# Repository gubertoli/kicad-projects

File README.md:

# kicad-projects
Some KiCAD PCB Designs

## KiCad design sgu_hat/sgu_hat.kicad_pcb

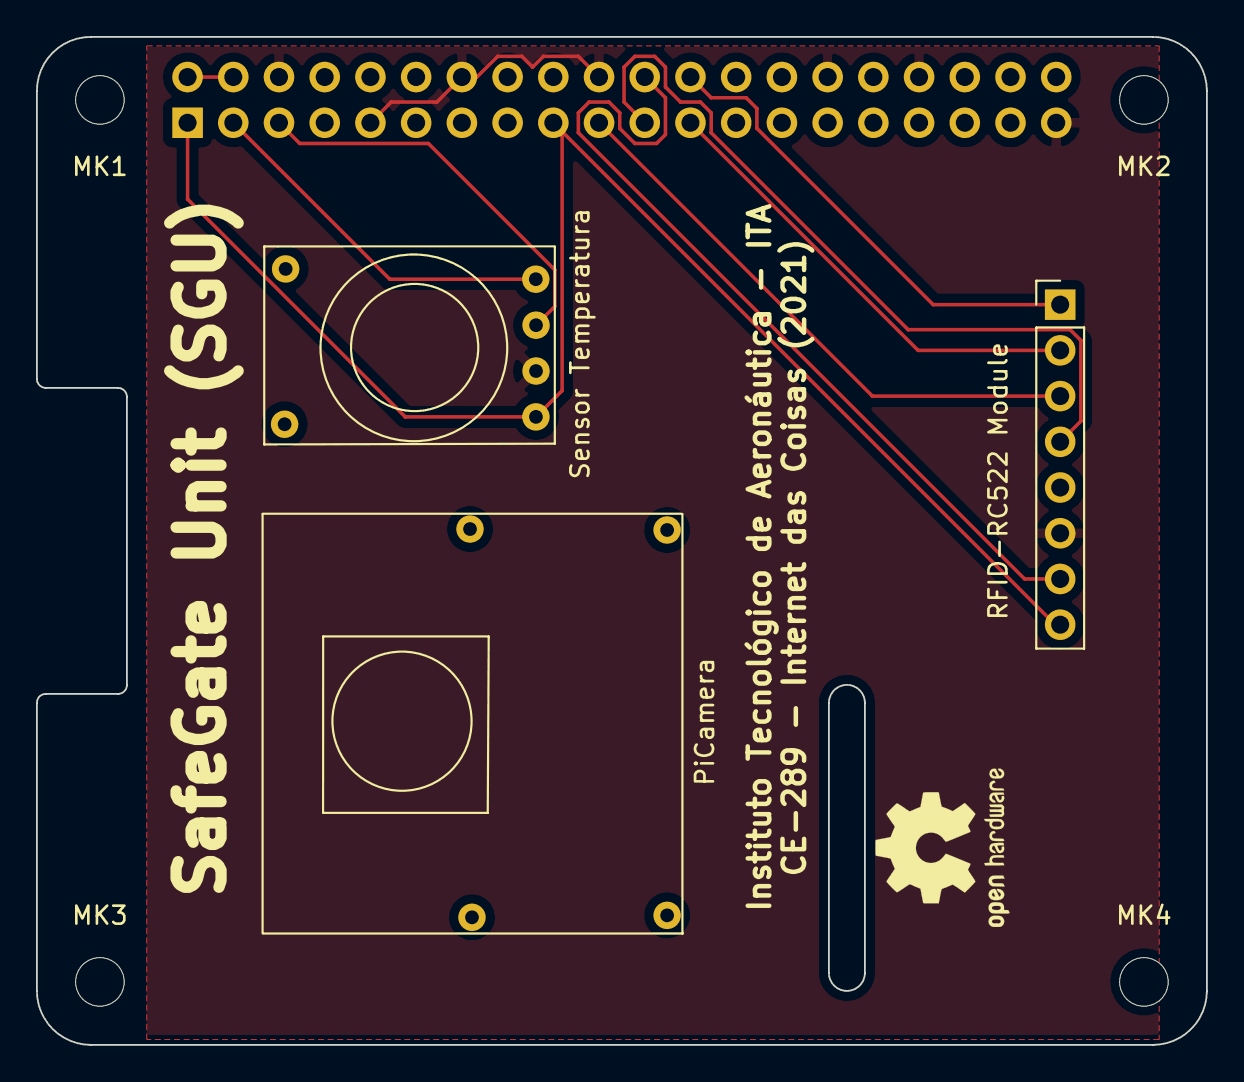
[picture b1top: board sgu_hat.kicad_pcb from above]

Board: 2 copper layers, 65.0 x 56.0 mm, 8 parts (1 on the bottom side), 10 nets.

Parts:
MK1, MK2, MK3, MK4: M2.5; MountingHole_2.7mm_M2.5
P1: Conn_02x20_Odd_Even; PinSocket_2x20_P2.54mm_Vertical
PiCamera: Camera_Lens; PiCamera
RFID-RC522 Module: RFID-RC522-MODULE; PinHeader_1x08_P2.54mm_Vertical
Sensor Temperatura: MLX90614ESF-AAA-000-TU; MLX90614_Shield

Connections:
+3V3: P1.1, P1.17, RFID-RC522 Module.8, Sensor Temperatura.VIN
+5V: P1.2, P1.4
/GPIO2(SDA1): P1.3, Sensor Temperatura.1
/GPIO3(SCL1): P1.5, Sensor Temperatura.SCL
/GPIO8(SPI0_CE_N): P1.24, RFID-RC522 Module.1
/GPIO9(SPI0_MISO): P1.21, RFID-RC522 Module.4
/GPIO10(SPI0_MOSI): P1.19, RFID-RC522 Module.3
/GPIO11(SPI0_SCK): P1.23, RFID-RC522 Module.2
/GPIO25(GEN6): P1.22, RFID-RC522 Module.7
GND: P1.6, P1.9, P1.14, P1.20, P1.25, P1.30, P1.34, P1.39, RFID-RC522 Module.6, Sensor Temperatura.GND

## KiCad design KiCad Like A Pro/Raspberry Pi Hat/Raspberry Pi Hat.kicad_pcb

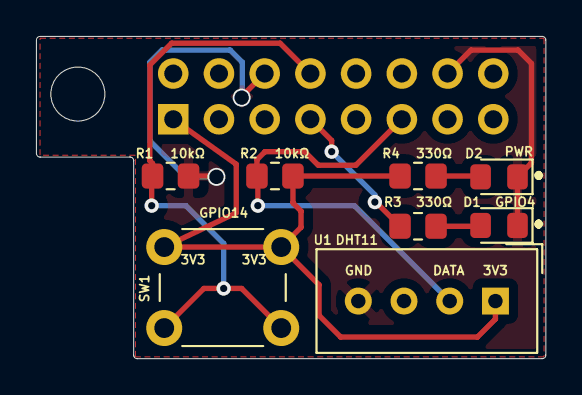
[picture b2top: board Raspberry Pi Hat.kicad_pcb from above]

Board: 2 copper layers, 28.3 x 17.9 mm, 9 parts (1 on the bottom side), 7 nets.

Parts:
D1: GPIO4; LED_0805_2012Metric_Pad1.15x1.40mm_HandSolder
D2: PWR; LED_0805_2012Metric_Pad1.15x1.40mm_HandSolder
J1: Raspberry_Pi_2_3; PinSocket_2x08_P2.54mm_Vertical
R1, R2: 10kΩ; R_0805_2012Metric_Pad1.20x1.40mm_HandSolder
R3, R4: 330Ω; R_0805_2012Metric_Pad1.20x1.40mm_HandSolder
SW1: GPIO14; SW_PUSH_6mm
U1: DHT11; Aosong_DHT11_5.5x12.0_P2.54mm

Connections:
/3V3: J1.1, R2.2, R4.1, SW1.1, U1.1
/BUTTON: J1.8, R1.1, SW1.2
/DHT: J1.11, R2.1, U1.2
GND: D1.1, D2.1, J1.6, J1.9, J1.14, R1.2, U1.4
unnamed: D1.2, R3.2
unnamed: D2.2, R4.2
unnamed: J1.7, R3.1

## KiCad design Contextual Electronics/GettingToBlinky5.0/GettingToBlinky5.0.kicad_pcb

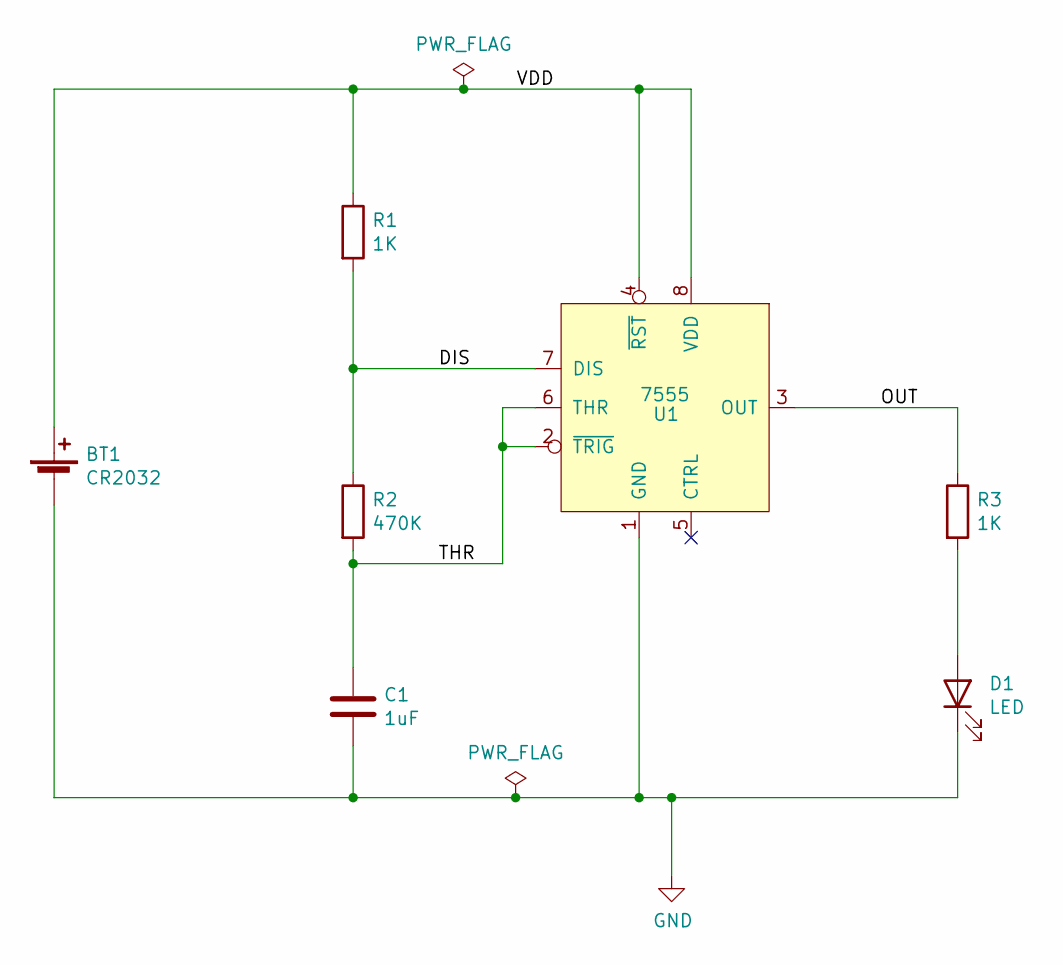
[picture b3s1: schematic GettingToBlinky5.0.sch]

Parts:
BT1: CR2032; S8211-46R
C1: 1uF; C_0805_2012Metric_Pad1.18x1.45mm_HandSolder
D1: LED; LED_0805_2012Metric_Pad1.15x1.40mm_HandSolder
R1, R3: 1K; R_0805_2012Metric_Pad1.20x1.40mm_HandSolder
R2: 470K; R_0805_2012Metric_Pad1.20x1.40mm_HandSolder
U1: 7555; SOIC-8_3.9x4.9mm_P1.27mm

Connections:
/DIS: R1.2, R2.1, U1.7 (DIS)
/OUT: R3.1, U1.3 (OUT)
/THR: C1.1, R2.2, U1.2 (~TRIG), U1.6 (THR)
/VDD: BT1.1 (+), R1.1, U1.4 (~RST), U1.8 (VDD)
GND: BT1.2 (-), C1.2, D1.1 (K), U1.1 (GND)
unnamed: D1.2 (A), R3.2

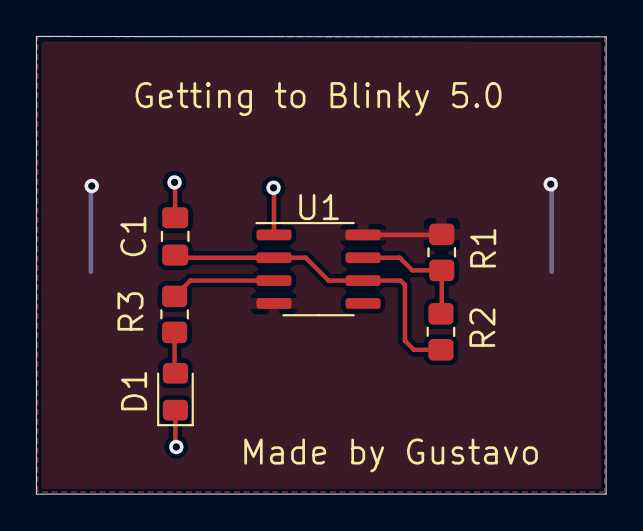
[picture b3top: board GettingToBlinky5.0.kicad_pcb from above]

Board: 2 copper layers, 31.6 x 25.4 mm, 7 parts (1 on the bottom side), 6 nets.

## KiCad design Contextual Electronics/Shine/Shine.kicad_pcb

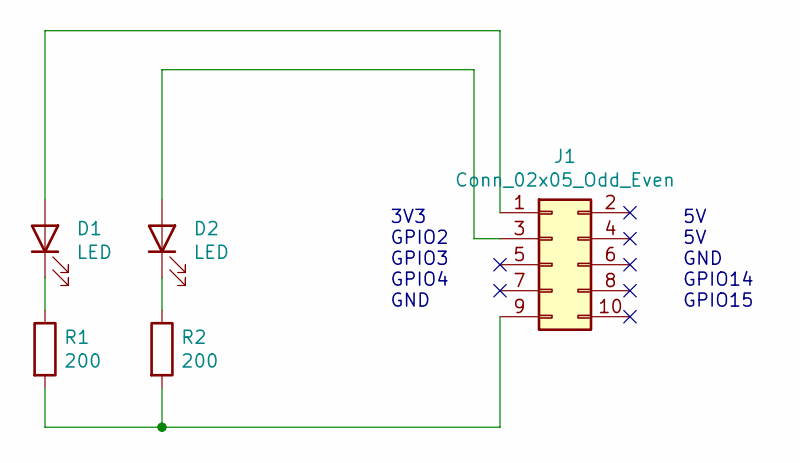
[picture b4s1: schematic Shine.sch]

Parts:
D1, D2: LED; LED_1206_3216Metric_Pad1.42x1.75mm_HandSolder
J1: Conn_02x05_Odd_Even; PinHeader_2x05_P2.54mm_Vertical
R1, R2: 200; R_1206_3216Metric_Pad1.30x1.75mm_HandSolder

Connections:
unnamed: D1.1 (K), R1.1
unnamed: D1.2 (A), J1.1
unnamed: D2.1 (K), R2.1
unnamed: D2.2 (A), J1.3
unnamed: J1.9, R1.2, R2.2

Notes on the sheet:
3V3 GPIO2 GPIO3 GPIO4 GND
5V 5V GND GPIO14 GPIO15

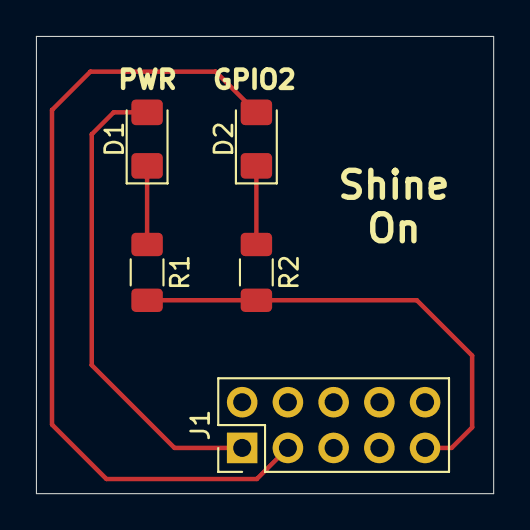
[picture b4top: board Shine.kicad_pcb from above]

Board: 2 copper layers, 25.4 x 25.4 mm, 5 parts (0 on the bottom side), 5 nets.

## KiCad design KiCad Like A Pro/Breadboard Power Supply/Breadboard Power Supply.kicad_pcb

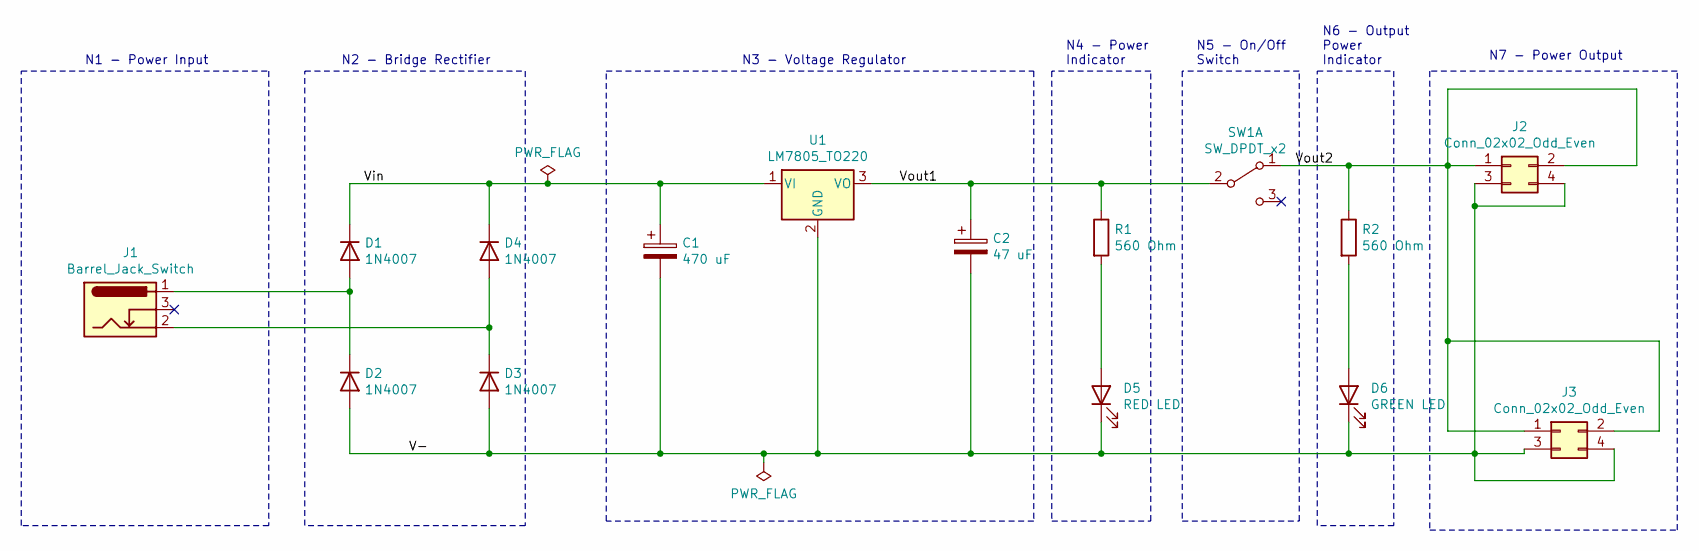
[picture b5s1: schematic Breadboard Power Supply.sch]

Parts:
C1: 470 uF; CP_Radial_D10.0mm_P5.00mm
C2: 47 uF; CP_Radial_D6.3mm_P2.50mm
D1, D2, D3, D4: 1N4007; D_DO-41_SOD81_P10.16mm_Horizontal
D5: RED LED; LED_D5.0mm
D6: GREEN LED; LED_D5.0mm
J1: Barrel_Jack_Switch; BarrelJack_CUI_PJ-102AH_Horizontal
J2, J3: Conn_02x02_Odd_Even; PinHeader_2x02_P2.54mm_Vertical
R1, R2: 560 Ohm; R_Axial_DIN0207_L6.3mm_D2.5mm_P7.62mm_Horizontal
SW1: SW_DPDT_x2; Switch_Slide_11.6x4mm_EG1218
U1: LM7805_TO220; TO-220-3_Vertical

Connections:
/V-: C1.2, C2.2, D2.2 (A), D3.2 (A), D5.1 (K), D6.1 (K), J2.3, J2.4, J3.3, J3.4, U1.2 (GND)
/Vin: C1.1, D1.1 (K), D4.1 (K), U1.1 (VI)
/Vout1: C2.1, R1.1, SW1.2 (B), U1.3 (VO)
/Vout2: J2.1, J2.2, J3.1, J3.2, R2.1, SW1.1 (A)
unnamed: D1.2 (A), D2.1 (K), J1.1
unnamed: D3.1 (K), D4.2 (A), J1.2
unnamed: D5.2 (A), R1.2
unnamed: D6.2 (A), R2.2

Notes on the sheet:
N1 - Power Input
N2 - Bridge Rectifier
N3 - Voltage Regulator
N4 - Power Indicator
N5 - On/Off Switch
N6 - Output Power Indicator
N7 - Power Output

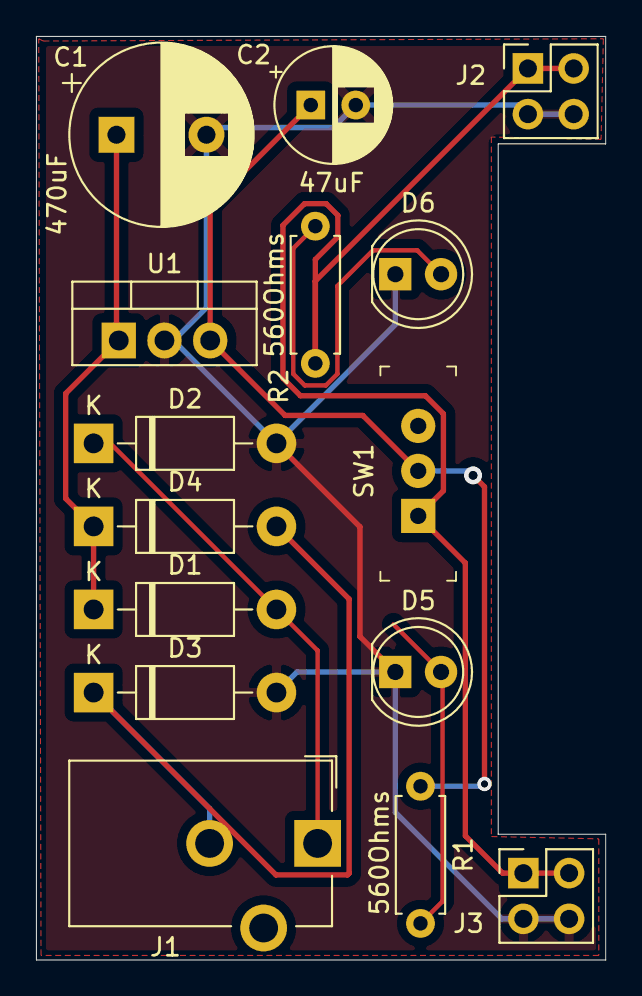
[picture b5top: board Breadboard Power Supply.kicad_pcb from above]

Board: 2 copper layers, 31.6 x 51.3 mm, 15 parts (0 on the bottom side), 8 nets.

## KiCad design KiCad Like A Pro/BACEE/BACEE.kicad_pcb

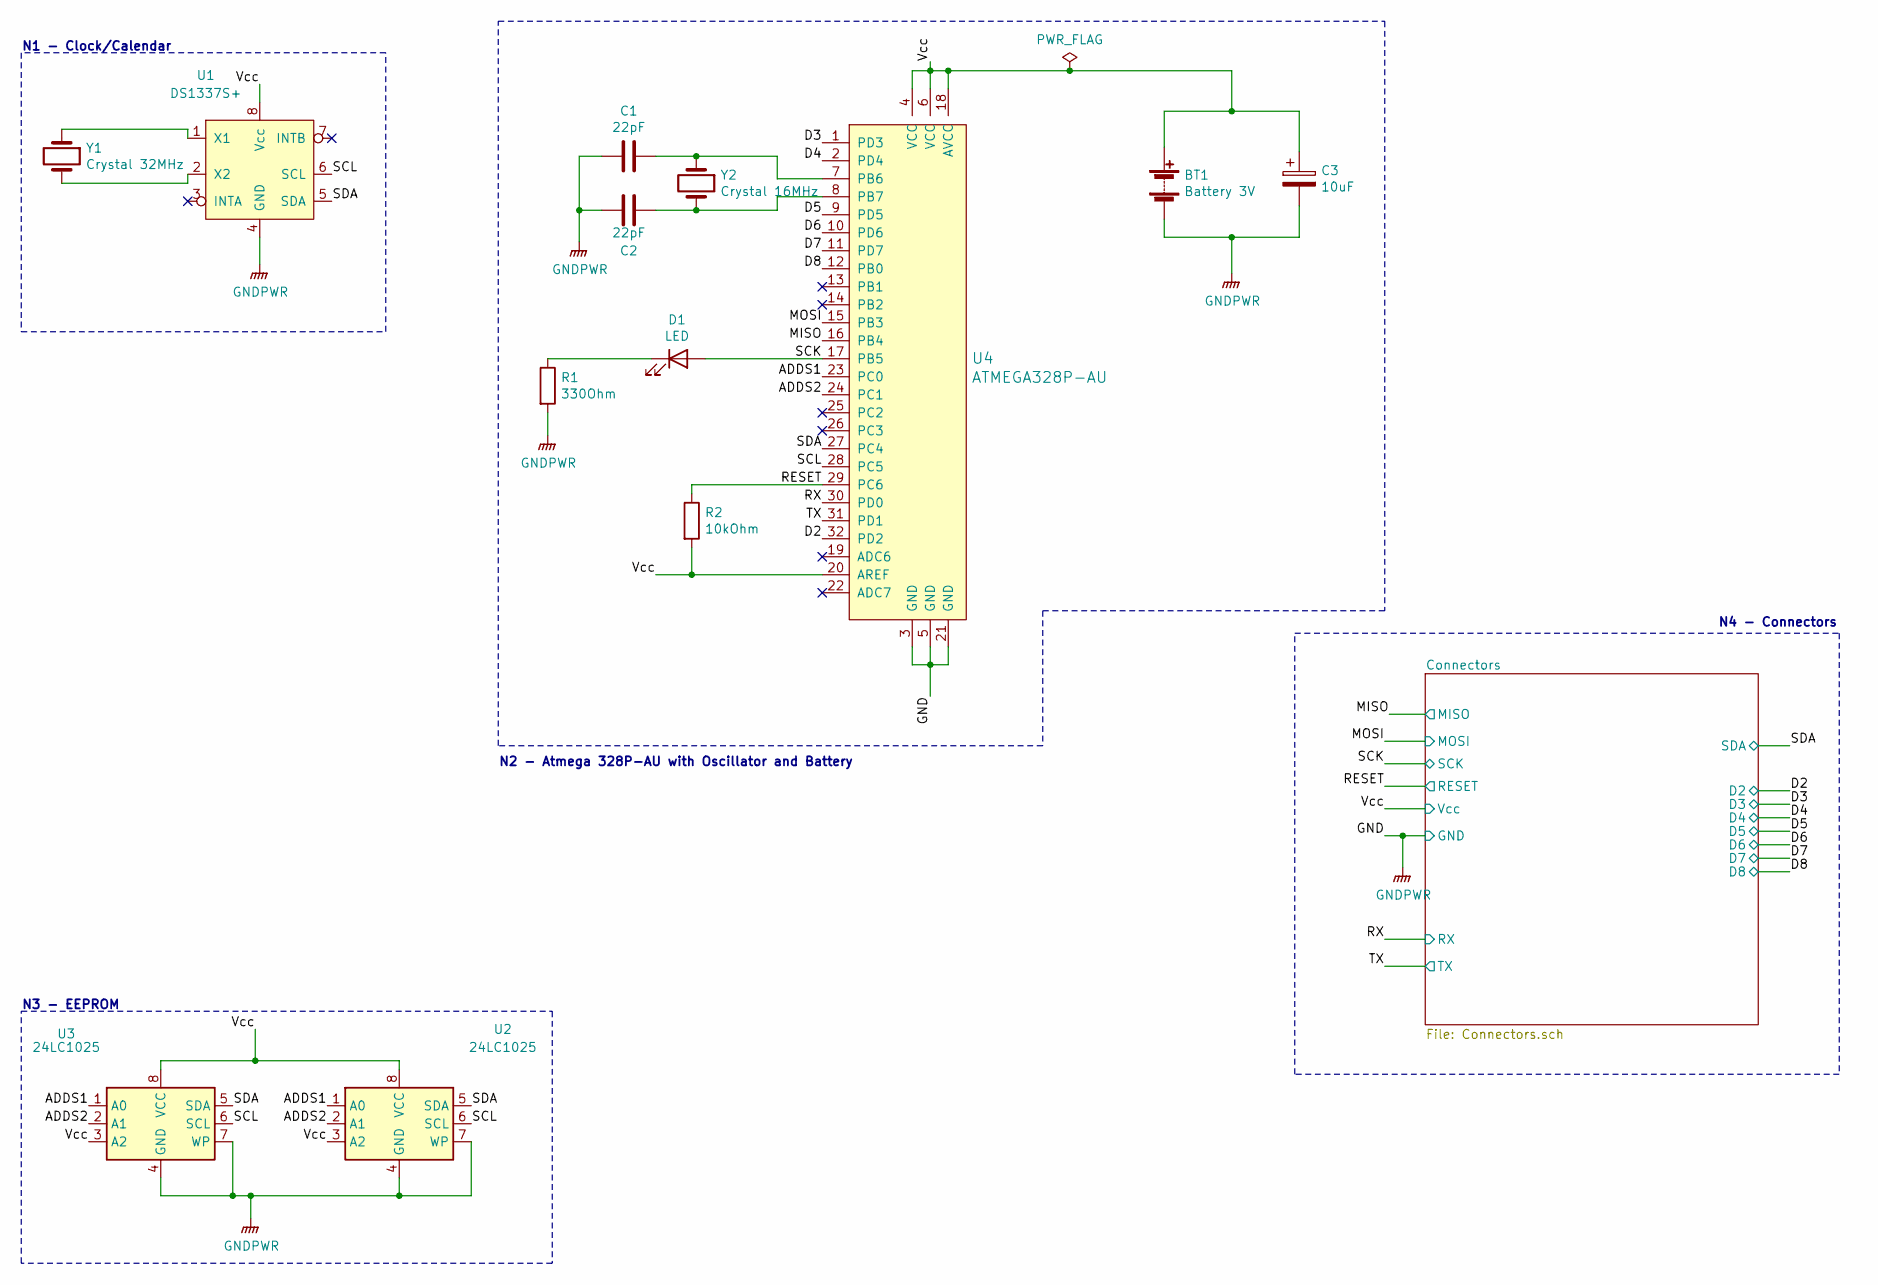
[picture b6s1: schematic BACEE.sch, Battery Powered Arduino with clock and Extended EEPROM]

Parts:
BT1: Battery 3V; PinHeader_1x02_P2.54mm_Vertical
C1, C2: 22pF; C_0805_2012Metric_Pad1.18x1.45mm_HandSolder
C3: 10uF; C_0805_2012Metric_Pad1.18x1.45mm_HandSolder
D1: LED; LED_0805_2012Metric_Pad1.15x1.40mm_HandSolder
R1: 330Ohm; R_0805_2012Metric_Pad1.20x1.40mm_HandSolder
R2: 10kOhm; R_0805_2012Metric_Pad1.20x1.40mm_HandSolder
U1: DS1337S+; SO-8_5.3x6.2mm_P1.27mm
U2, U3: 24LC1025; SOIJ-8_5.3x5.3mm_P1.27mm
U4: ATMEGA328P-AU; TQFP-32_7x7mm; MPN ATMEGA328P-AU; Digi-Key_PN ATMEGA328P-AU-ND
Y1: Crystal 32MHz; Crystal_SMD_MicroCrystal_CC7V-T1A-2Pin_3.2x1.5mm_HandSolder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
Y2: Crystal 16MHz; Crystal_SMD_5032-2Pin_5.0x3.2mm_HandSoldering

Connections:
/ADDS1: U2.1 (A0), U3.1 (A0), U4.23 (PC0)
/ADDS2: U2.2 (A1), U3.2 (A1), U4.24 (PC1)
/D2: U4.32 (PD2); also elsewhere on the board
/D3: U4.1 (PD3); also elsewhere on the board
/D4: U4.2 (PD4); also elsewhere on the board
/D5: U4.9 (PD5); also elsewhere on the board
/D6: U4.10 (PD6); also elsewhere on the board
/D7: U4.11 (PD7); also elsewhere on the board
/D8: U4.12 (PB0); also elsewhere on the board
/MISO: U4.16 (PB4); also elsewhere on the board
/MOSI: U4.15 (PB3); also elsewhere on the board
/RESET: R2.1, U4.29 (PC6); also elsewhere on the board
/RX: U4.30 (PD0); also elsewhere on the board
/SCK: D1.2 (A), U4.17 (PB5); also elsewhere on the board
/SCL: U1.6 (SCL), U2.6 (SCL), U3.6 (SCL), U4.28 (PC5)
/SDA: U1.5 (SDA), U2.5 (SDA), U3.5 (SDA), U4.27 (PC4); also elsewhere on the board
/TX: U4.31 (PD1); also elsewhere on the board
/Vcc: BT1.1 (+), C3.1, R2.2, U1.8 (Vcc), U2.3 (A2), U2.8 (VCC), U3.3 (A2), U3.8 (VCC), U4.4 (VCC), U4.6 (VCC), U4.18 (AVCC), U4.20 (AREF); also elsewhere on the board
GNDPWR: BT1.2 (-), C1.2, C2.1, C3.2, R1.2, U1.4 (GND), U2.4 (GND), U2.7 (WP), U3.4 (GND), U3.7 (WP), U4.3 (GND), U4.5 (GND), U4.21 (GND); also elsewhere on the board
unnamed: C1.1, U4.7 (PB6), Y2.1
unnamed: C2.2, U4.8 (PB7), Y2.2
unnamed: D1.1 (K), R1.1
unnamed: U1.1 (X1), Y1.1
unnamed: U1.2 (X2), Y1.2

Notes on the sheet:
N1 - Clock/Calendar
N3 - EEPROM
N2 - Atmega 328P-AU with Oscillator and Battery
N4 - Connectors

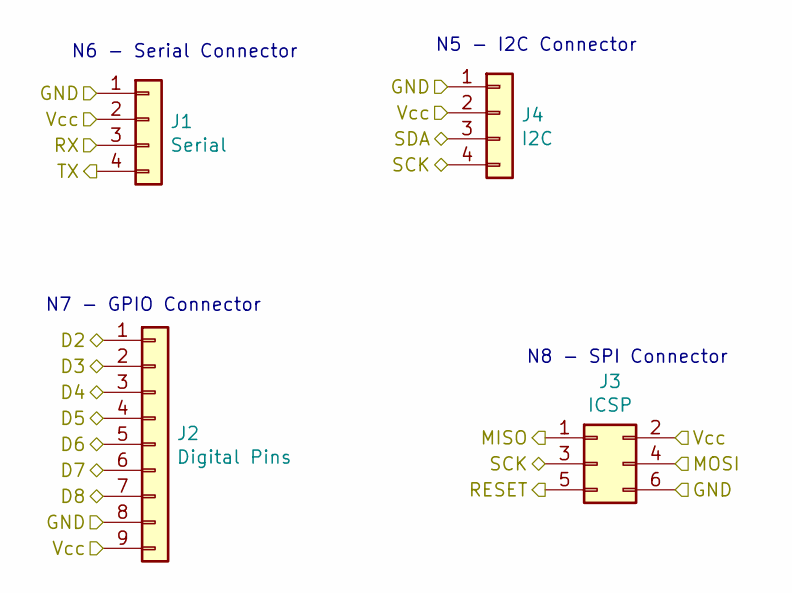
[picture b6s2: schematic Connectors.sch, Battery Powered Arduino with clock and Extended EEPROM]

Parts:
J1: Serial; PinSocket_1x04_P2.54mm_Vertical
J2: Digital Pins; PinSocket_1x09_P2.54mm_Vertical
J3: ICSP; PinSocket_2x03_P2.54mm_Vertical
J4: I2C; PinSocket_1x04_P2.54mm_Vertical

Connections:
/D2: J2.1; also elsewhere on the board
/D3: J2.2; also elsewhere on the board
/D4: J2.3; also elsewhere on the board
/D5: J2.4; also elsewhere on the board
/D6: J2.5; also elsewhere on the board
/D7: J2.6; also elsewhere on the board
/D8: J2.7; also elsewhere on the board
/MISO: J3.1; also elsewhere on the board
/MOSI: J3.4; also elsewhere on the board
/RESET: J3.5; also elsewhere on the board
/RX: J1.3; also elsewhere on the board
/SCK: J3.3, J4.4; also elsewhere on the board
/SDA: J4.3; also elsewhere on the board
/TX: J1.4; also elsewhere on the board
/Vcc: J1.2, J2.9, J3.2, J4.2; also elsewhere on the board
GNDPWR: J1.1, J2.8, J3.6, J4.1; also elsewhere on the board

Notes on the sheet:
N6 - Serial Connector
N5 - I2C Connector
N7 - GPIO Connector
N8 - SPI Connector

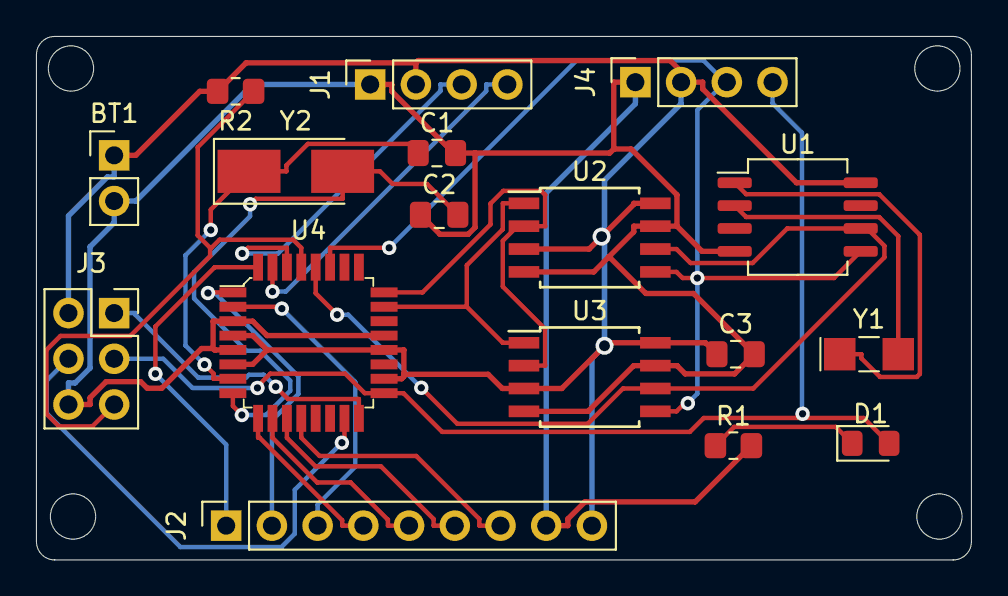
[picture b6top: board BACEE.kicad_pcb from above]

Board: 4 copper layers, 51.9 x 29.1 mm, 17 parts (0 on the bottom side), 24 nets.

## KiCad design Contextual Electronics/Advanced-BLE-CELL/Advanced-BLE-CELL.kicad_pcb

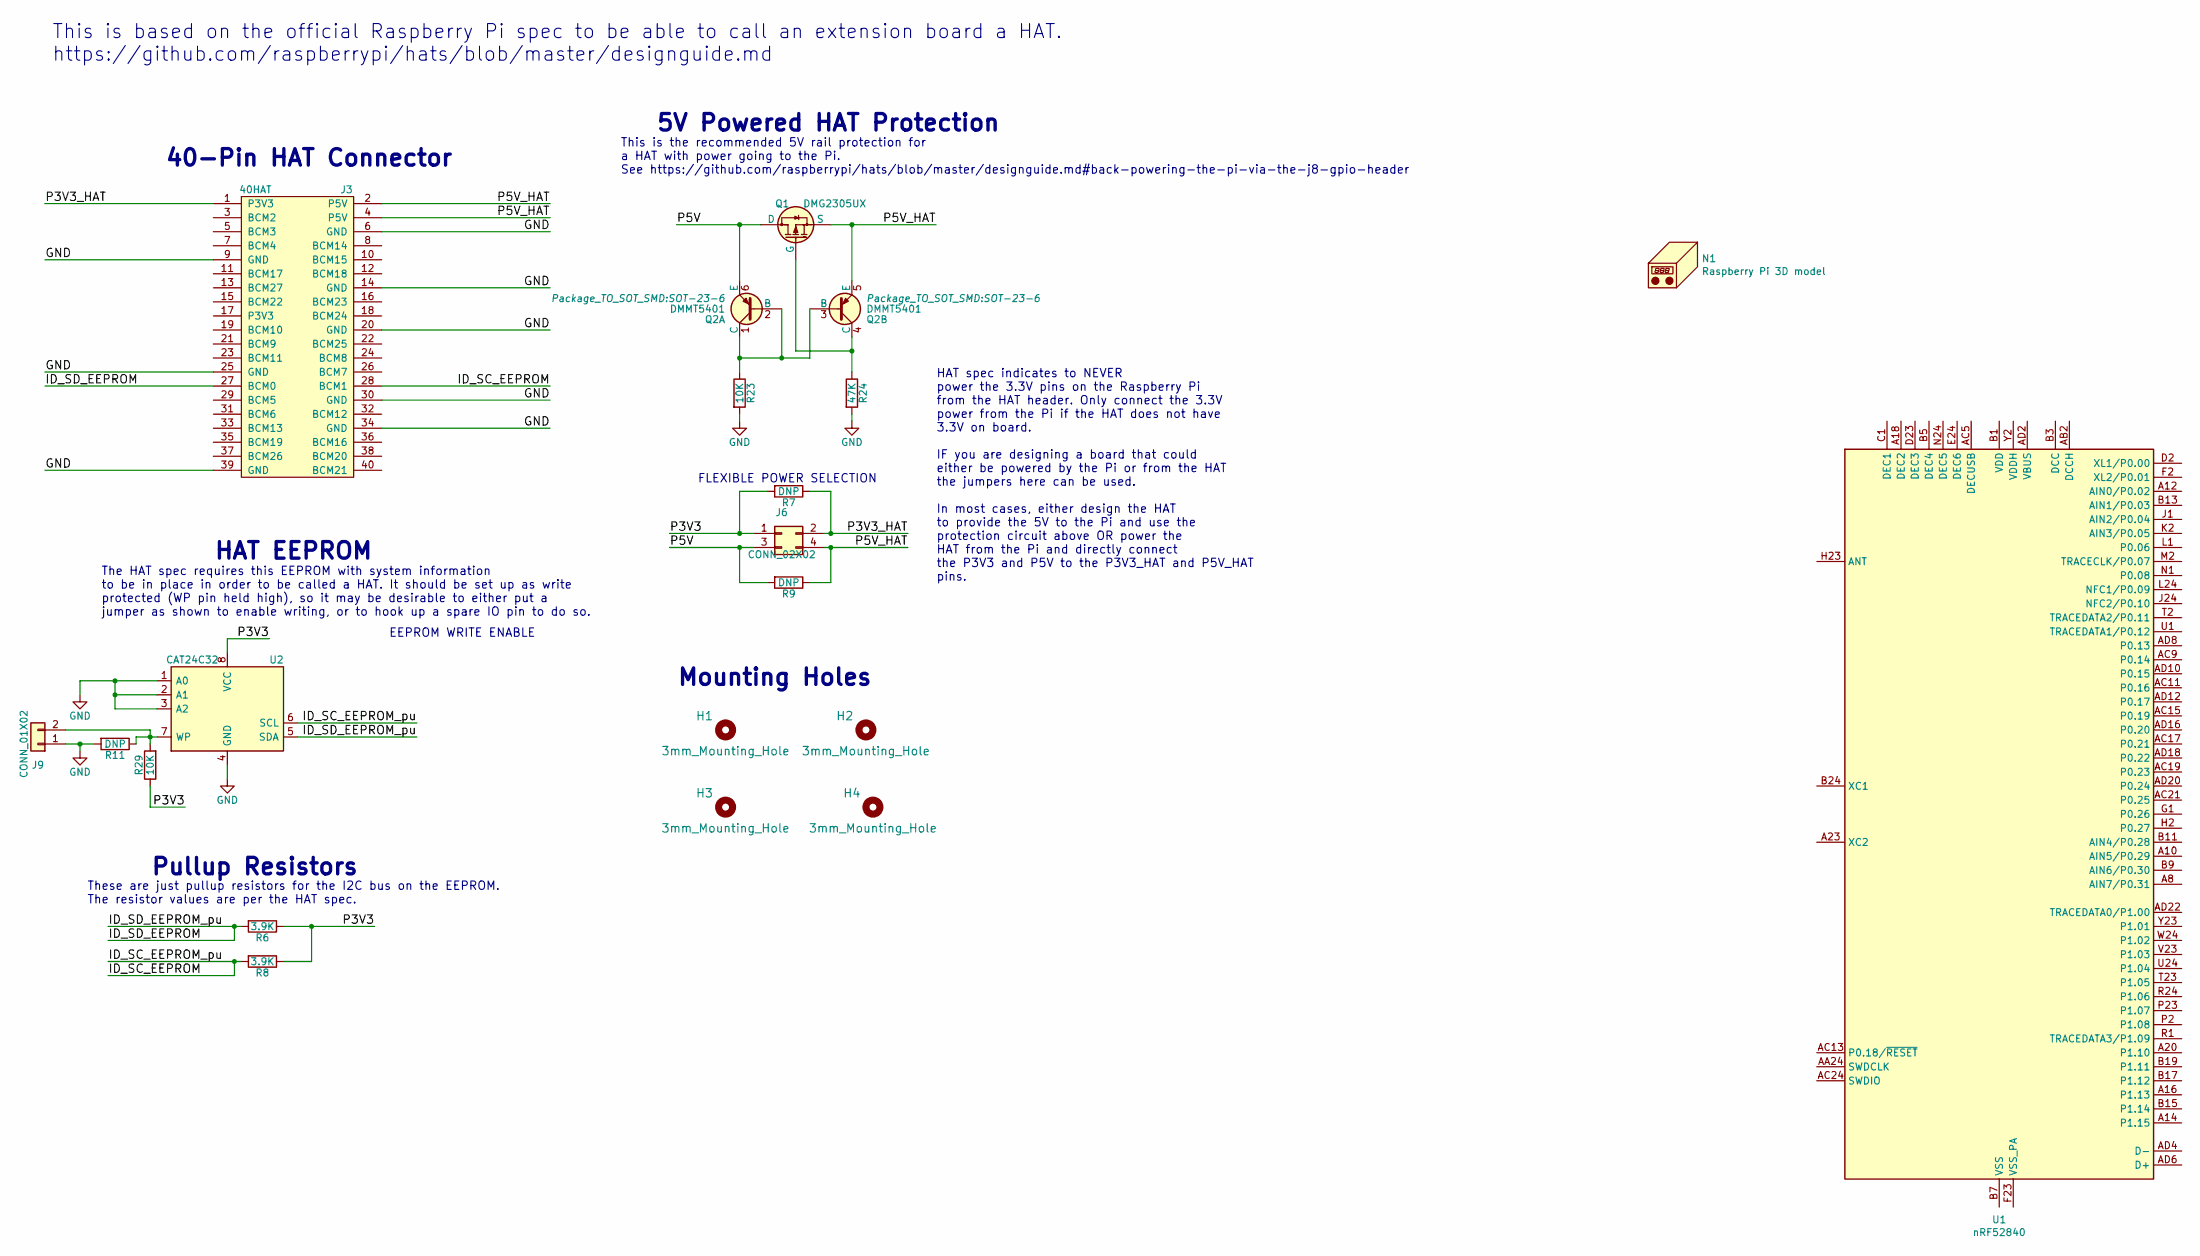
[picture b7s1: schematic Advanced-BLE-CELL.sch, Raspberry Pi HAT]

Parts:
H1, H2, H3, H4: 3mm_Mounting_Hole; NPTH_3mm_ID
J3: 40HAT; PinSocket_2x20_P2.54mm_Vertical
J6: CONN_02X02; PinHeader_2x02_P2.54mm_Vertical
J9: CONN_01X02; PinHeader_1x02_P2.54mm_Vertical
N1: Raspberry Pi 3D model
Q1: DMG2305UX; SOT-23
Q2: DMMT5401; SOT-23-6
R6, R8: 3.9K; R_0603_1608Metric_Pad0.84x1.00mm_HandSolder
R7, R9, R11: DNP; R_0603_1608Metric_Pad0.84x1.00mm_HandSolder
R23, R29: 10K; R_0603_1608Metric_Pad0.84x1.00mm_HandSolder
R24: 47K; R_0603_1608Metric_Pad0.84x1.00mm_HandSolder
U1: nRF52840; Nordic_AQFN-73-1EP_7x7mm_P0.5mm
U2: CAT24C32; SOIC-8_3.9x4.9mm_P1.27mm

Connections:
/ID_SC_EEPROM: J3.28 (BCM1), R8.2, U2.6 (SCL)
/ID_SD_EEPROM: J3.27 (BCM0), R6.2, U2.5 (SDA)
/P3V3: J6.1, R6.1, R7.2, R8.1, R29.1, U2.8 (VCC)
/P3V3_HAT: J3.1 (P3V3), J6.2, R7.1
/P5V: J6.3, Q1.3 (D), Q2.6 (E), R9.2
/P5V_HAT: J3.2 (P5V), J3.4 (P5V), J6.4, Q1.2 (S), Q2.5 (E), R9.1
GND: J3.6 (GND), J3.9 (GND), J3.14 (GND), J3.20 (GND), J3.25 (GND), J3.30 (GND), J3.34 (GND), J3.39 (GND), J9.1, R11.2, R23.2, R24.2, U2.1 (A0), U2.2 (A1), U2.3 (A2), U2.4 (GND)
unnamed: J9.2, R11.1, R29.2, U2.7 (WP)
unnamed: Q1.1 (G), Q2.4 (C), R24.1
unnamed: Q2.1 (C), Q2.2 (B), Q2.3 (B), R23.1
unnamed: U1.A22 (VDD), U1.AD14 (VDD), U1.AD23 (VDD), U1.B1 (VDD), U1.W1 (VDD)
unnamed: U1.B7 (VSS), U1.EP (VSS)

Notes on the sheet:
FLEXIBLE POWER SELECTION
5V Powered HAT Protection
This is the recommended 5V rail protection for a HAT with power going to the Pi. See https://github.com/raspberrypi/hats/blob/master/designguide.md#back-powering-the-pi-via-the-j8-gpio-header
EEPROM WRITE ENABLE
Pullup Resistors
HAT EEPROM
Mounting Holes
40-Pin HAT Connector
HAT spec indicates to NEVER power the 3.3V pins on the Raspberry Pi from the HAT header. Only connect the 3.3V power from the Pi if the HAT does not have 3.3V on board. IF you are designing a board that could either be powered by the Pi or from the HAT the jumpers here can be used. In most cases, e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
The HAT spec requires this EEPROM with system information to be in place in order to be called a HAT. It should be set up as write protected (WP pin held high), so it may be desirable to either put a jumper as shown to enable writing, or to hook up a spare IO pin to do so.
These are just pullup resistors for the I2C bus on the EEPROM. The resistor values are per the HAT spec.
This is based on the official Raspberry Pi spec to be able to call an extension board a HAT. https://github.com/raspberrypi/hats/blob/master/designguide.md

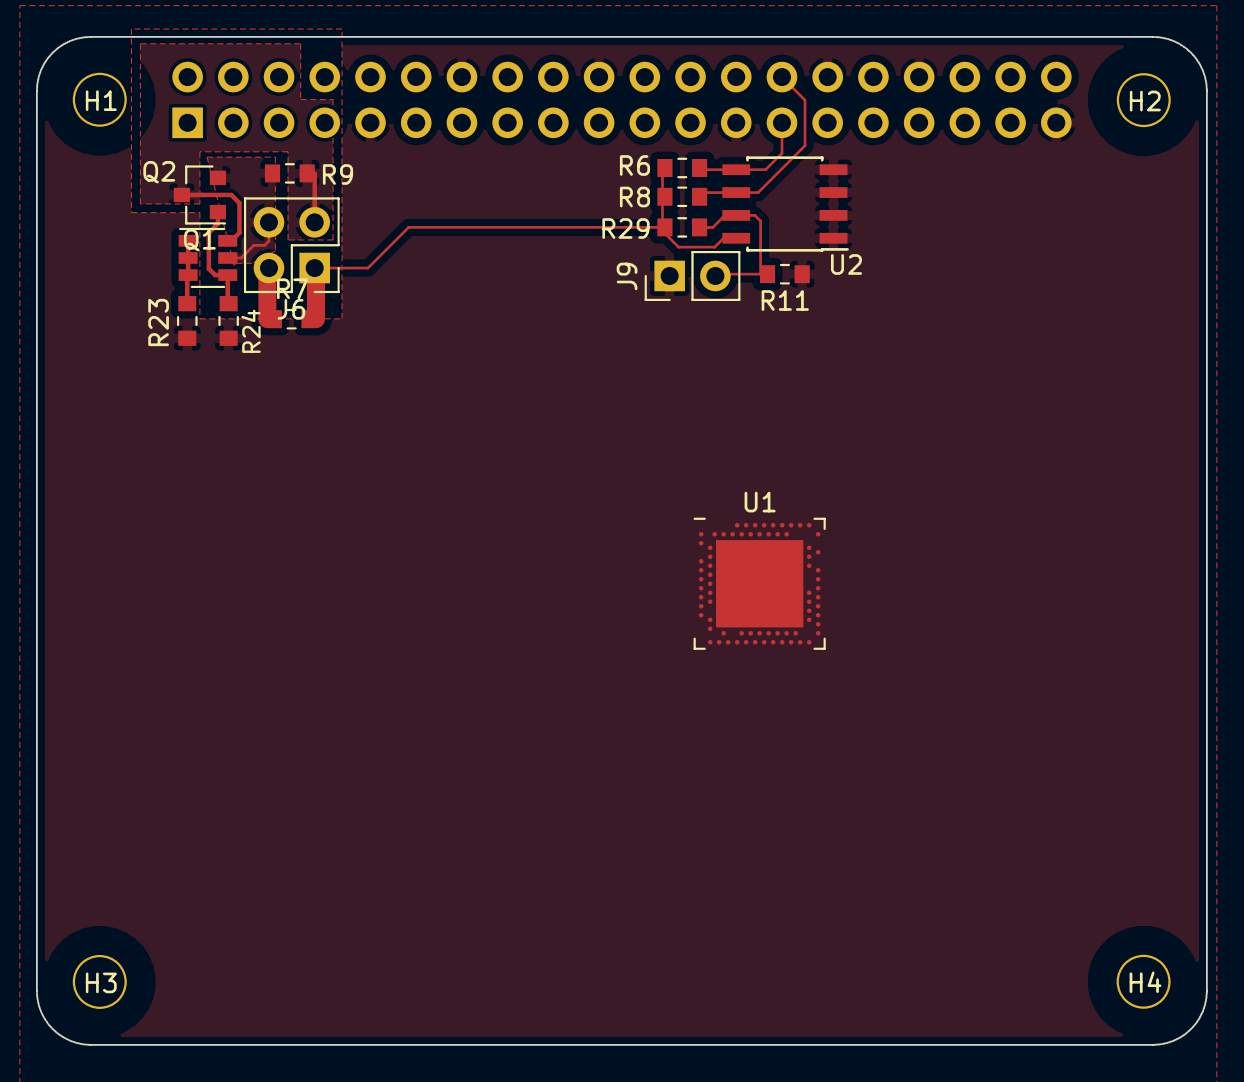
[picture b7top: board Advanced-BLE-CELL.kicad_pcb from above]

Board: 4 copper layers, 65.0 x 56.0 mm, 19 parts (1 on the bottom side), 12 nets.

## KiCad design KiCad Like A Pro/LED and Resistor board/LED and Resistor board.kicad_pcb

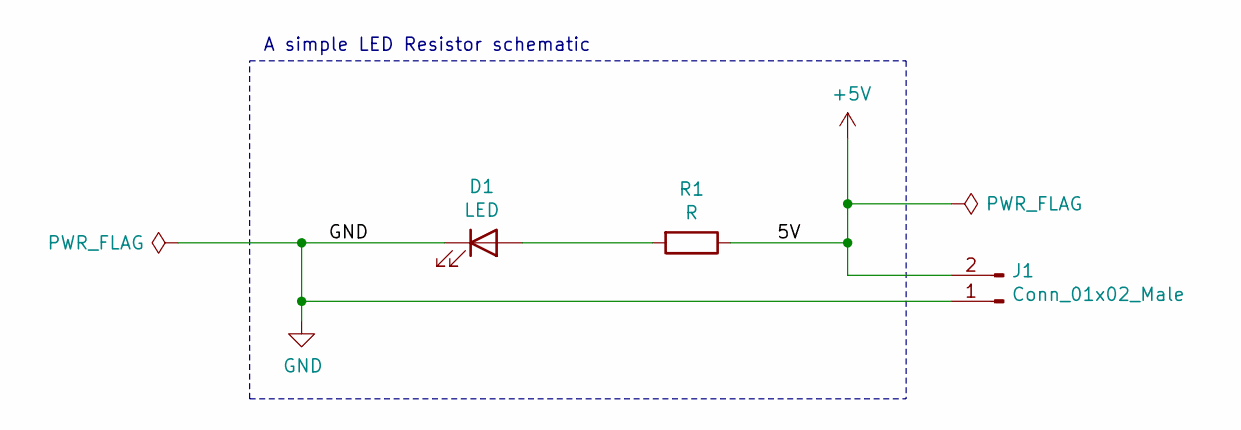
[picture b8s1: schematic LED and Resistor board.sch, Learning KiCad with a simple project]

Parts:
D1: LED; LED_D8.0mm
J1: Conn_01x02_Male; TerminalBlock_bornier-2_P5.08mm
R1: R; R_Axial_DIN0204_L3.6mm_D1.6mm_P5.08mm_Horizontal

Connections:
+5V: J1.2, R1.1
GND: D1.1 (K), J1.1
unnamed: D1.2 (A), R1.2

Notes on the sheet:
A simple LED Resistor schematic

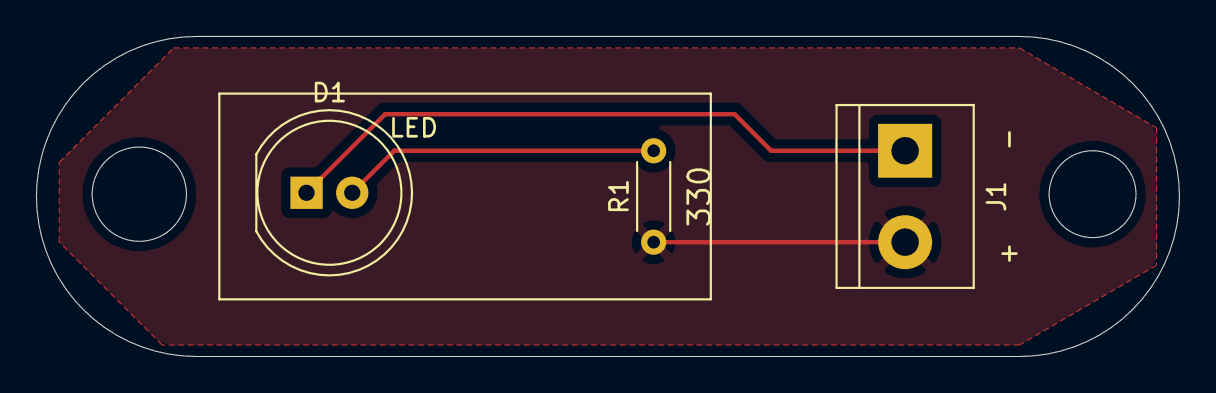
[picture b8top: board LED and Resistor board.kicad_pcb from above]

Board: 2 copper layers, 63.5 x 17.8 mm, 3 parts (0 on the bottom side), 3 nets.

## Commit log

2021-01-19 First commit
    First commit
2021-01-21 Initial files for nodeLHC
2021-06-22 SGU for CE-289
